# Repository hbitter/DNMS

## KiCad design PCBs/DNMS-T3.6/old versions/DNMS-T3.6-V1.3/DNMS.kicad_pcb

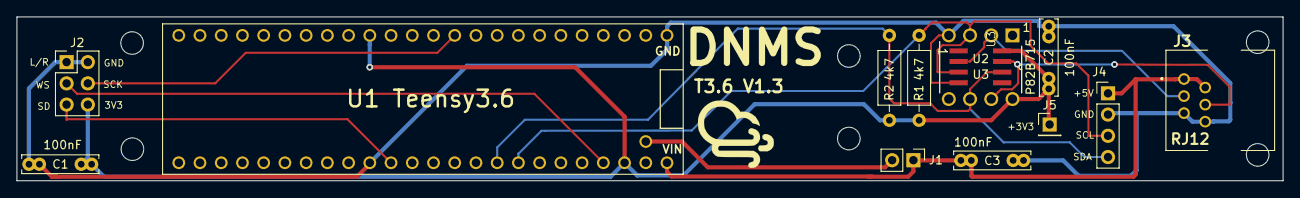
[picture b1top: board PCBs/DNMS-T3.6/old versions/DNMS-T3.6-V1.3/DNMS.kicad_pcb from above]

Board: 2 copper layers, 151.5 x 19.6 mm, 19 parts (0 on the bottom side), 11 nets.

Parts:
C1, C2, C3: 100nF; C_THT_100nF_L9.0mm_W2.0mm_P5.00mm_P7.50mm
J1: Conn_01x02; PinHeader_1x02_P2.54mm_Vertical
J2: Conn_02x03_Odd_Even; PinHeader_2x03_P2.54mm_Vertical
J3: RJ12; RJ12_Pulse_E5566Q0LK22L
J4: Conn_01x04; PinHeader_1x04_P2.54mm_Vertical
J5: Conn_01x01; PinHeader_1x01_P2.54mm_Vertical
R1, R2: 4k7; R_Axial_DIN0207_L6.3mm_D2.5mm_P10.16mm_Horizontal
REF1, REF1#2, REF1#3, REF1#4, REF1#5, REF1#6: MountingHole_2.7mm_M2.5
U1 Teensy3.6: VAL**; Teensy3.6
U2: P82B715; DIP254P762X420-8
U3: P82B715DR; SOIC8

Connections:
+3V3: C1.1, C2.1, J2.6, J5.1, R1.1, R2.1, U1 Teensy3.6.3V3_1, U1 Teensy3.6.3V3_2, U2.8, U3.8
+5V: C3.1, J1.1, J3.1, J3.2, J4.1, U1 Teensy3.6.VIN
GND: C1.2, C2.2, C3.2, J2.1, J2.2, J3.5, J3.6, J4.2, U1 Teensy3.6.GND_1, U1 Teensy3.6.GND_2, U2.4, U3.4
unnamed: J1.2, U1 Teensy3.6.VUSB
SCK: J2.4, U1 Teensy3.6.9
SCL: J4.3, R1.2, U1 Teensy3.6.19, U2.3, U3.3
SCL_Ex: J3.3, U2.2, U3.2
SD: J2.5, U1 Teensy3.6.13
SDA: J4.4, R2.2, U1 Teensy3.6.18, U2.6, U3.6
SDA_Ex: J3.4, U2.7, U3.7
WS: J2.3, U1 Teensy3.6.23

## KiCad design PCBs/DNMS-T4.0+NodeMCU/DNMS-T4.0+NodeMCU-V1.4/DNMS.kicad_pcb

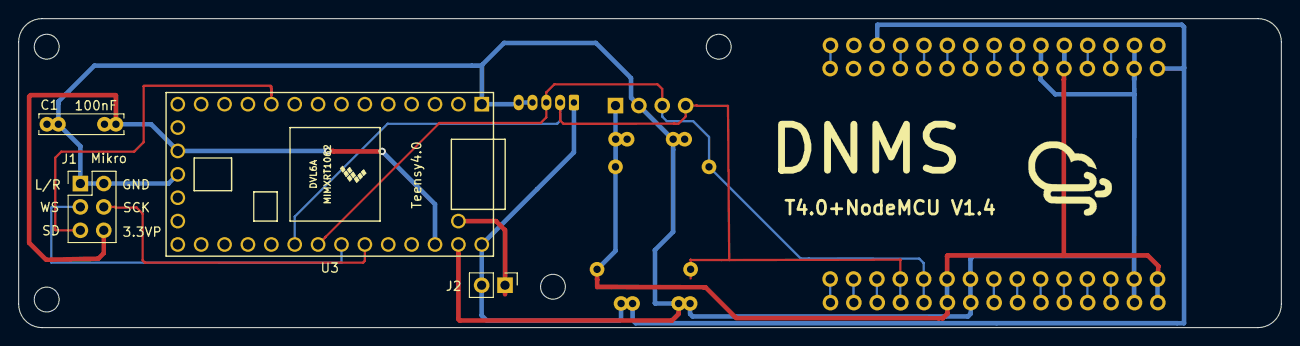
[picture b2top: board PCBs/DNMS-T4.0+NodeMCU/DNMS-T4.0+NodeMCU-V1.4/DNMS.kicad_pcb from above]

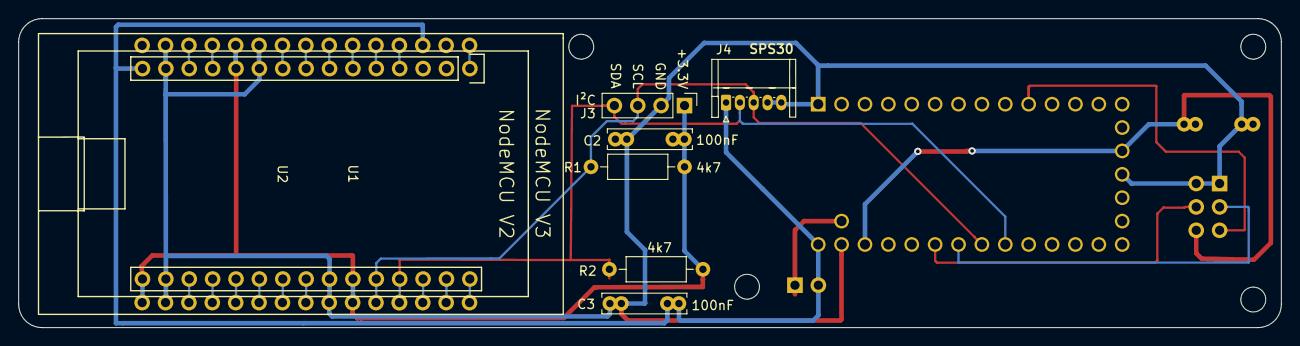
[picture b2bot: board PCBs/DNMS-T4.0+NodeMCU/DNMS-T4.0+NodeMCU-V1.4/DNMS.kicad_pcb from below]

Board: 2 copper layers, 137.2 x 33.6 mm, 16 parts (8 on the bottom side), 28 nets.

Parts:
C1, C2, C3: 100nF; C_THT_100nF_L9.0mm_W2.0mm_P5.00mm_P7.50mm
J1: Conn_02x03_Odd_Even; PinHeader_2x03_P2.54mm_Vertical
J2: Conn_01x02; PinHeader_1x02_P2.54mm_Vertical
J3: Conn_01x04; PinHeader_1x04_P2.54mm_Vertical
J4: Conn_01x05; JST_ZH_S5B-EH_1x05_P1.50mm_Horizontal
R1, R2: 4k7; R_Axial_DIN0207_L6.3mm_D2.5mm_P10.16mm_Horizontal
REF1, REF1#2, REF1#3, REF1#4: MountingHole_2.7mm_M2.5
U1: NodeMCU V2; NodeMCU_V2
U2: NodeMCU V3; NodeMCU_V3
U3: Teensy4.0; Teensy40

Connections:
+3.3VP: C1.1, J1.6, U3.16, U3.31
+3V3: C2.1, J3.1, R1.1, R2.1, U1.11, U1.16, U1.25, U2.11, U2.16, U2.25
+5V: C3.1, J2.2, J4.1, U1.15, U2.3, U3.33
GND: C1.2, C2.2, C3.2, J1.1, J1.2, J3.2, J4.4, J4.5, U1.10, U1.14, U1.17, U1.24, U2.10, U2.14, U2.17, U2.24, U3.1, U3.17, U3.32
unnamed: J2.1, U3.34
unnamed: U1.1, U2.1
unnamed: U1.4, U2.4
unnamed: U1.5, U2.5
unnamed: U1.6, U2.6
unnamed: U1.7, U2.7
unnamed: U1.8, U2.8
unnamed: U1.9, U2.9
unnamed: U1.12, U2.12
unnamed: U1.13, U2.13
unnamed: U1.18, U2.18
unnamed: U1.19, U2.19
unnamed: U1.20, U2.20
unnamed: U1.21, U2.21
unnamed: U1.22, U2.22
unnamed: U1.23, U2.23
unnamed: U1.28, U2.28
unnamed: U1.29, U2.29
unnamed: U1.30, U2.30
SCK: J1.4, U3.28
SCL: J3.3, J4.3, R1.2, U1.26, U2.26, U3.26
SD: J1.5, U3.10
SDA: J3.4, J4.2, R2.2, U1.27, U2.27, U3.25
WS: J1.3, U3.27

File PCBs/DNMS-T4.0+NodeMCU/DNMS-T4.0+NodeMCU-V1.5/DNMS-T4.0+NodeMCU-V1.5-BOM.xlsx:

BOM | DNMS-T4.0+NodeMCU-V1.5
Item # | Reference | Qty | Manufacturer | Manufacturer Part # | Description / Value | Package/Footprint | Type | Distributor | Distributor # | Link to Distributor | Link to alternate Source | Link to alternate Source | Notes | Price (single Qty) Mouser | Price
1 | C1, C2, C3 | 3 | Vishay | K104K15X7RF53H5L | Multilayer Ceramic Capacitors MLCC - Leaded 0.1uF 50volts 10% X7R 5mm LS | 5mm LS | THT | Mouser | 594-K104K15X7RF53H5 | Mouser | Reichelt | Voelkner | any other Manufacturer is ok | 0.085 | 0.255
2 | J1 | 1 | Würth | 61200621721 | Sockel & Kabelgehäuse WR-BHD 2.54mm Male 6P Angl Gold BoX Hdr | P2.54mm 2x3 | THT | Mouser | 710-61200621721 | Mouser | Reichelt | Voelkner | any other Manufacturer is ok | 0.923 | 0.923
3 | J2 | 1 | Amphenol FCI | 10129378-902001BLF | PIN Header 1x02 P2.54mm vertical | P2.54mm | THT | Mouser | 649-1012937890201BLF | Mouser | Reichelt | Voelkner | any other Manufacturer is ok | 0.085 | 0.085
4 | J3 | 1 | Amphenol Commercial Products | G800W304018EU | Pin Header 2.54mm Pitch STR DIP,1x4Pin,FULL G/F,NY6T,6.1mm*2.5mm*3.0mm,Color-Bl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 | P2,54mm | THT | Mouser | 523-G800W304018EU | Mouser | Reichelt | Voelkner | any other Manufacturer is ok, (optional) | 0.085 | 0.085
5 | J5 | 1 | JST | S5B-ZR(LF)(SN) | Through-hole type shrouded header, siede entry | P1,5mm | THT | Voelkner | D19571 | Voelkner | smdv |  | (optional) | 0.53 | 0.53
6 | R1, R2 | 2 | Vishay | CCF074K70JKE36 | Metal Film Resistor 1/4watt 4.7Kohms 5% Rated to 1/2watt | 6,62mm axial | THT | Mouser | 71-CCF07-J-4.7K-E3 | Mouser | Reichelt | Voelkner | any other Manufacturer is ok, Kohleschicht oder Metallschicht, 0,25Watt oder 0,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 | 0.152 | 0.304
7 | U1 | 1 | diverse | NodeMCU V3 | NodeMCU ESP8266 Entwicklungs Board V3 | 58 x 31mm | THT | KOMPUTER DE | KP06014 | KOMPUTER DE | AZ-Delivery |  | either U1 or U2 as alternate assembly | 3.12 | 3.12
8 | U2 | 1 | diverse | NodeMCU V2 | ESP8266 NodeMCU V2 Delopment Board | 48 x 26mm | THT | AZ-Delivery | NodeMCU Lua Amica Modul V2 ESP8266 ESP-12F | AZ-Delivery | BerryBase |  | either U1 or U2 as alternate assembly | 5.79 | 5.79
9 | U3 | 1 | PJRC | TEENSY40 | Teensy 4.0 Development Board | 1.4 by 0.7 inch | THT | Antratek Electronics Deutschland | TEENSY40 | Antratek Electronics Deutschland | EXP GmbH |  |  | 19.6 | 19.6

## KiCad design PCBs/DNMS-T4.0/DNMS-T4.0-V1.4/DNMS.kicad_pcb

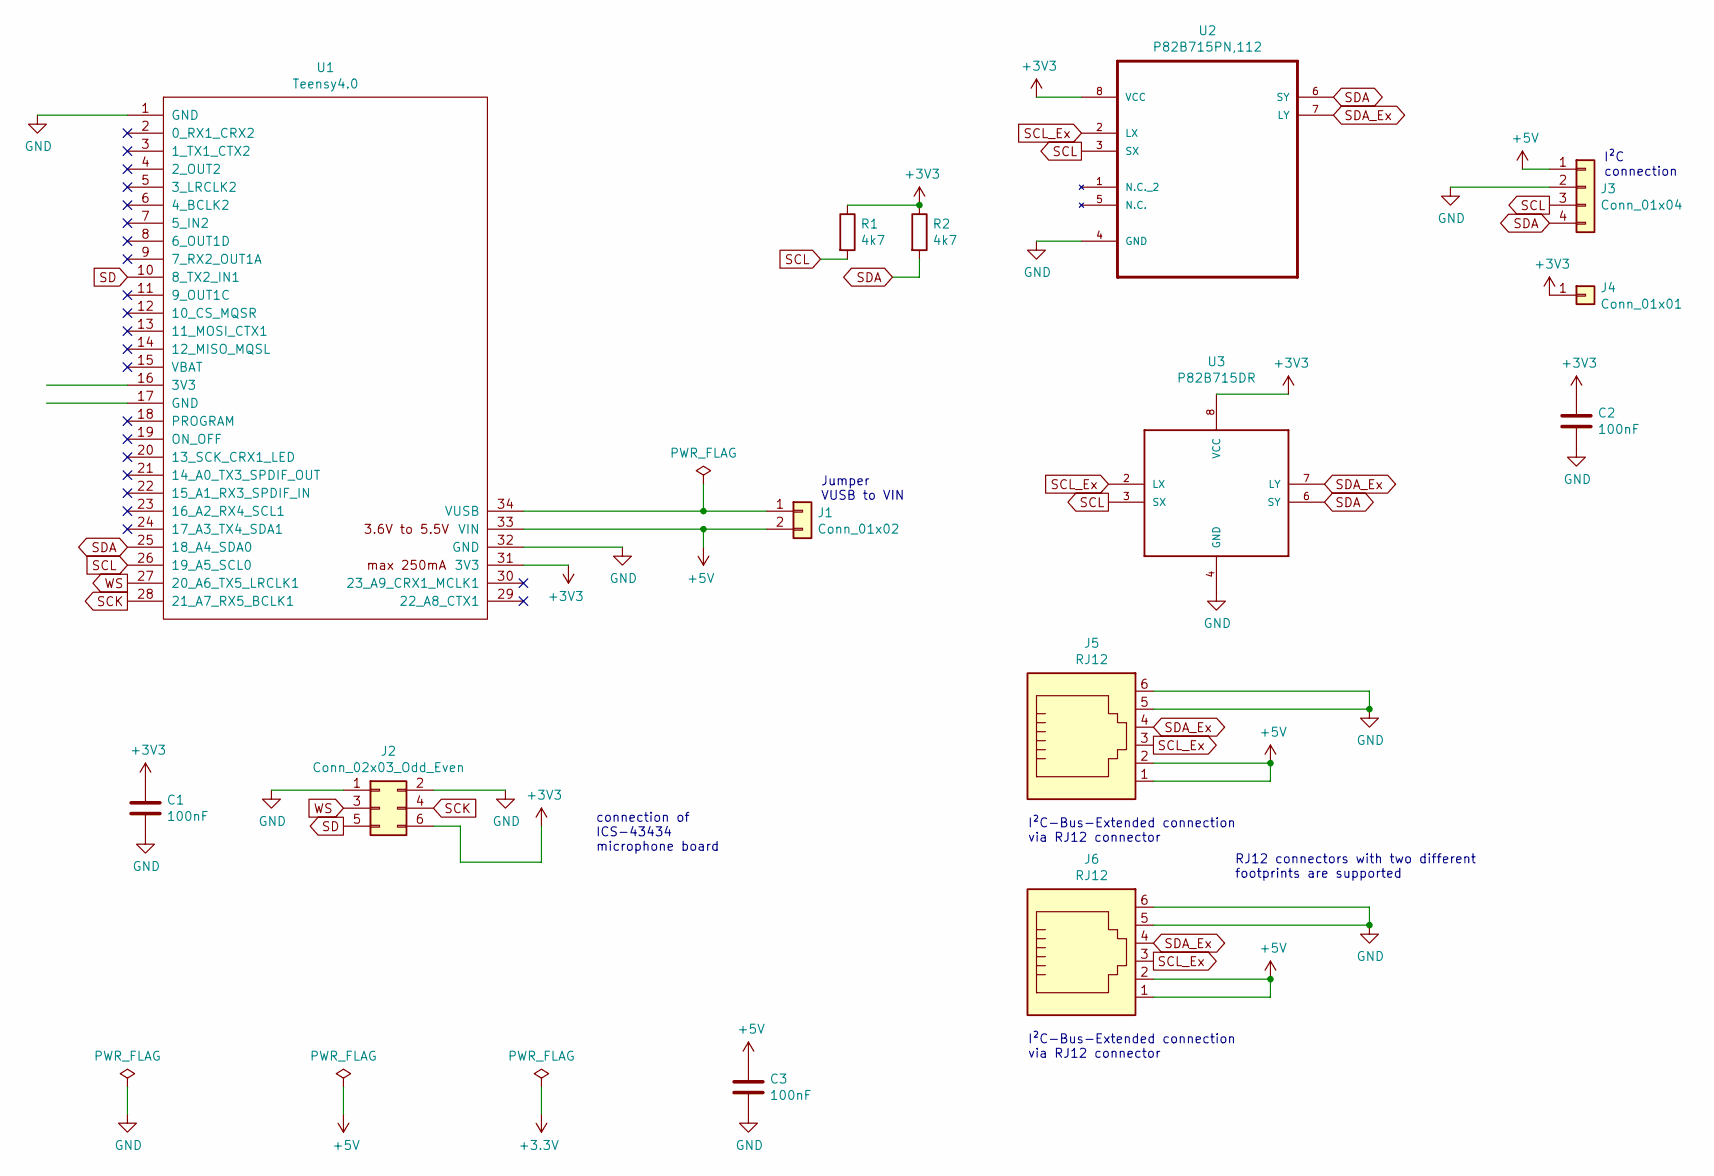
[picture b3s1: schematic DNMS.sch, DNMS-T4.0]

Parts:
C1, C2, C3: 100nF; C_THT_100nF_L9.0mm_W2.0mm_P5.00mm_P7.50mm
J1: Conn_01x02; PinHeader_1x02_P2.54mm_Vertical
J2: Conn_02x03_Odd_Even; PinHeader_2x03_P2.54mm_Vertical
J3: Conn_01x04; PinHeader_1x04_P2.54mm_Vertical
J4: Conn_01x01; PinHeader_1x01_P2.54mm_Vertical
J5: RJ12; RJ12_Amphenol_54601
J6: RJ12; RJ12_Pulse_E5566Q0LK22L
R1, R2: 4k7; R_Axial_DIN0207_L6.3mm_D2.5mm_P10.16mm_Horizontal
U1: Teensy4.0; Teensy40
U2: P82B715PN,112; DIP254P762X420-8
U3: P82B715DR; SOIC8

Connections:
+3V3: C1.1, C2.1, J2.6, J4.1, R1.1, R2.1, U1.31 (3V3), U2.8 (VCC), U3.8 (VCC)
+5V: C3.1, J1.2, J3.1, J5.1, J5.2, J6.1, J6.2, U1.33 (VIN)
GND: C1.2, C2.2, C3.2, J2.1, J2.2, J3.2, J5.5, J5.6, J6.5, J6.6, U1.1 (GND), U1.32 (GND), U2.4 (GND), U3.4 (GND)
unnamed: J1.1, U1.34 (VUSB)
SCK: J2.4, U1.28 (21_A7_RX5_BCLK1)
SCL: J3.3, R1.2, U1.26 (19_A5_SCL0), U2.3 (SX), U3.3 (SX)
SCL_Ex: J5.3, J6.3, U2.2 (LX), U3.2 (LX)
SD: J2.5, U1.10 (8_TX2_IN1)
SDA: J3.4, R2.2, U1.25 (18_A4_SDA0), U2.6 (SY), U3.6 (SY)
SDA_Ex: J5.4, J6.4, U2.7 (LY), U3.7 (LY)
WS: J2.3, U1.27 (20_A6_TX5_LRCLK1)

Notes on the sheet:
I²C connection
connection of ICS-43434 microphone board
Jumper VUSB to VIN
I²C-Bus-Extended connection via RJ12 connector
RJ12 connectors with two different footprints are supported

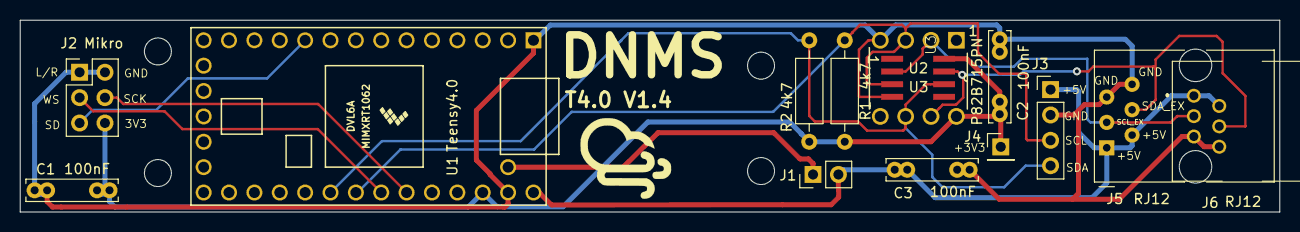
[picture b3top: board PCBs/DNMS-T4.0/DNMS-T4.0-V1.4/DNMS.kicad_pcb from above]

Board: 2 copper layers, 126.1 x 19.2 mm, 18 parts (0 on the bottom side), 11 nets.

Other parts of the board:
REF1, REF1#2, REF1#3, REF1#4: MountingHole_2.7mm_M2.5

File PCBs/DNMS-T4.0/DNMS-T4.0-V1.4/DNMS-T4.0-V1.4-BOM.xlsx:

BOM | DNMS-T4.0-V1.4
Item # | Reference | Qty | Manufacturer | Manufacturer Part # | Description / Value | Package/Footprint | Type | Distributor | Distributor # | Link to Distributor | Link to alternate Source | Link to alternate Source | Notes | Price (single Qty) Mouser | Price
1 | C1, C2, C3 | 3 | Vishay | K104K15X7RF53H5L | Multilayer Ceramic Capacitors MLCC - Leaded 0.1uF 50volts 10% X7R 5mm LS | 5mm LS | THT | Mouser | 594-K104K15X7RF53H5 | Mouser | Reichelt | Voelkner | any other Manufacturer is ok | 8.5000000000000006E-2 | 0.255
2 | J1 | 1 | Amphenol FCI | 10129378-902001BLF | PIN Header 1x02 P2.54mm vertical | P2.54mm | THT | Mouser | 649-1012937890201BLF | Mouser | Reichelt | Voelkner | any other Manufacturer is ok | 8.5000000000000006E-2 | 8.5000000000000006E-2
3 | J2 | 1 | Würth | 61200621721 | Sockel & Kabelgehäuse WR-BHD 2.54mm Male 6P Angl Gold BoX Hdr | P2.54mm 2x3 | THT | Mouser | 710-61200621721 | Mouser | Reichelt | Voelkner | any other Manufacturer is ok | 0.92300000000000004 | 0.92300000000000004
4 | J3 | 1 | Amphenol Commercial Products | G800W304018EU | Pin Header 2.54mm Pitch STR DIP,1x4Pin,FULL G/F,NY6T,6.1mm*2.5mm*3.0mm,Color-Bl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 | P2,54mm | THT | Mouser | 523-G800W304018EU | Mouser | Reichelt | Voelkner | any other Manufacturer is ok, (optional) | 8.5000000000000006E-2 | 8.5000000000000006E-2
5 | J4 | 1 | Samtec | TSW-101-07-T-S | PIN Header 1x01 P2.54mm vertical | P2,54mm | THT | Mouser | 200-TSW10107TS | Mouser | Reichelt |  | any other Manufacturer is ok, (optional) | 8.5000000000000006E-2 | 8.5000000000000006E-2
6 | J5 | 1 | Amphenol FCI | 54601-906WPLF | MOD JACK RJ12 6P6C CAT 3 HORIZ. 1 PORT |  | THT | Mouser | 649-54601-906WPLF | Mouser |  |  | either J5 or J6 as alternate assembly, this is the preferred assembly because o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 | 0.34699999999999998 | 0.34699999999999998
7 | J6 | 1 | Pulse Electronics | E5566-Q0LK22-L | Modular Jack RJ12/RJ25 6P6C SIDE ENTRY |  | THT | Mouser | 673-E5566-Q0LK22-L | Mouser | Reichelt | Voelkner | either J5 or J6 as alternate assembly, any other Manufacturer is ok | 0.44 | 0.44
8 | R1, R2 | 2 | Vishay | CCF074K70JKE36 | Metal Film Resistor 1/4watt 4.7Kohms 5% Rated to 1/2watt | 6,62mm axial | THT | Mouser | 71-CCF07-J-4.7K-E3 | Mouser | Reichelt | Voelkner | any other Manufacturer is ok, Kohleschicht oder Metallschicht, 0,25Watt oder 0,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 | 0.152 | 0.30399999999999999
9 | U1 | 1 | PJRC | TEENSY40 | Teensy 4.0 Development Board | 1.4 by 0.7 inch | THT | Antratek Electronics Deutschland | TEENSY40 | Antratek Electronics Deutschland | EXP GmbH |  |  | 19.600000000000001 | 19.600000000000001
10 | U2 | 1 | Texas Instruments | P82B715P | Signal Buffer, Verstärker I2C Bus Extender | DIP8 | THT | Mouser | 595-P82B715P | Mouser |  |  | either U2 or U3 as alternate assembly, any other Manufacturer is ok |  | 0
11 | U3 | 1 | Texas Instruments | P82B715DR | Signal Buffer, Verstärker I2C Bus Extender | SOIC8 | SMD | Mouser | 595-P82B715DR | Mouser | Reichelt |  | either U2 or U3 as alternate assembly, any other Manufacturer is ok | 1.58 | 1.58

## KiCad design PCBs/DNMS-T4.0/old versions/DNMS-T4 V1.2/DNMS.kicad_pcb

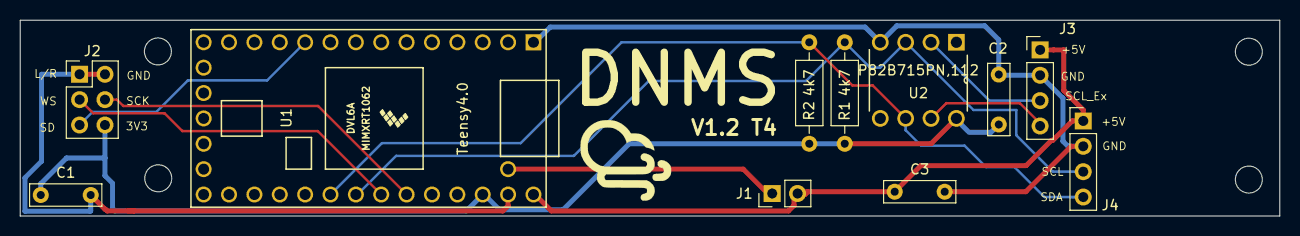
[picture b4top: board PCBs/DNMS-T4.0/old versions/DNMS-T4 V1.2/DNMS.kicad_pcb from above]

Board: 2 copper layers, 126.1 x 19.6 mm, 15 parts (0 on the bottom side), 11 nets.

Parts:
C1, C2, C3: 100nF; C_Rect_L7.0mm_W2.0mm_P5.00mm
J1: Conn_01x02; PinHeader_1x02_P2.54mm_Vertical
J2: Conn_2Rows-07Pins; PinHeader_2x03_P2.54mm_Vertical
J3, J4: Conn_01x04; PinHeader_1x04_P2.54mm_Vertical
R1, R2: 4k7; R_Axial_DIN0207_L6.3mm_D2.5mm_P10.16mm_Horizontal
REF1, REF1#2, REF1#3, REF2: MountingHole_2.7mm_M2.5
U1: Teensy4.0; Teensy40
U2: P82B715PN,112; DIP254P762X420-8

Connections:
+3V3: C1.1, C2.1, J2.6, R1.1, R2.1, U1.31, U2.8
+5V: C3.1, J1.2, J3.1, J4.1, U1.33
GND: C1.2, C2.2, C3.2, J2.1, J2.2, J3.2, J4.2, U1.1, U1.32, U2.4
unnamed: J1.1, U1.34
SCK: J2.4, U1.28
SCL: J4.3, R1.2, U1.26, U2.3
SCL_Ex: J3.3, U2.2
SD: J2.5, U1.10
SDA: J4.4, R2.2, U1.25, U2.6
SDA_Ex: J3.4, U2.7
WS: J2.3, U1.27

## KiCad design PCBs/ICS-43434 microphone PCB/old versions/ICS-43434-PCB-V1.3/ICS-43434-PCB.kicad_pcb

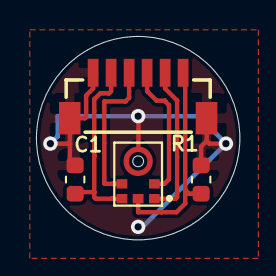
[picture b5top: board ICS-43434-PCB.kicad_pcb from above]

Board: 2 copper layers, 11.3 x 11.3 mm, 4 parts (0 on the bottom side), 6 nets.

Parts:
C1: 100nF; C_0603_1608Metric
J1: BM06B-SRSS-TB_LF__SN_; BM06BSRSSTBLFSN
MK1: ICS-43434; MIC_ICS-43434
R1: 100k; R_0603_1608Metric

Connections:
+3V3: C1.1, J1.2, MK1.5
GND: C1.2, J1.1, J1.MP1, J1.MP2, MK1.3, R1.2
LR: J1.4, MK1.2
SCK: J1.3, MK1.4
SD: J1.6, MK1.6, R1.1
WS: J1.5, MK1.1
